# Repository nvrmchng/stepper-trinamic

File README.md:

# stepper-trinamic
Driving stepper motor with TMC2130 IC from TRINAMIC Motion.

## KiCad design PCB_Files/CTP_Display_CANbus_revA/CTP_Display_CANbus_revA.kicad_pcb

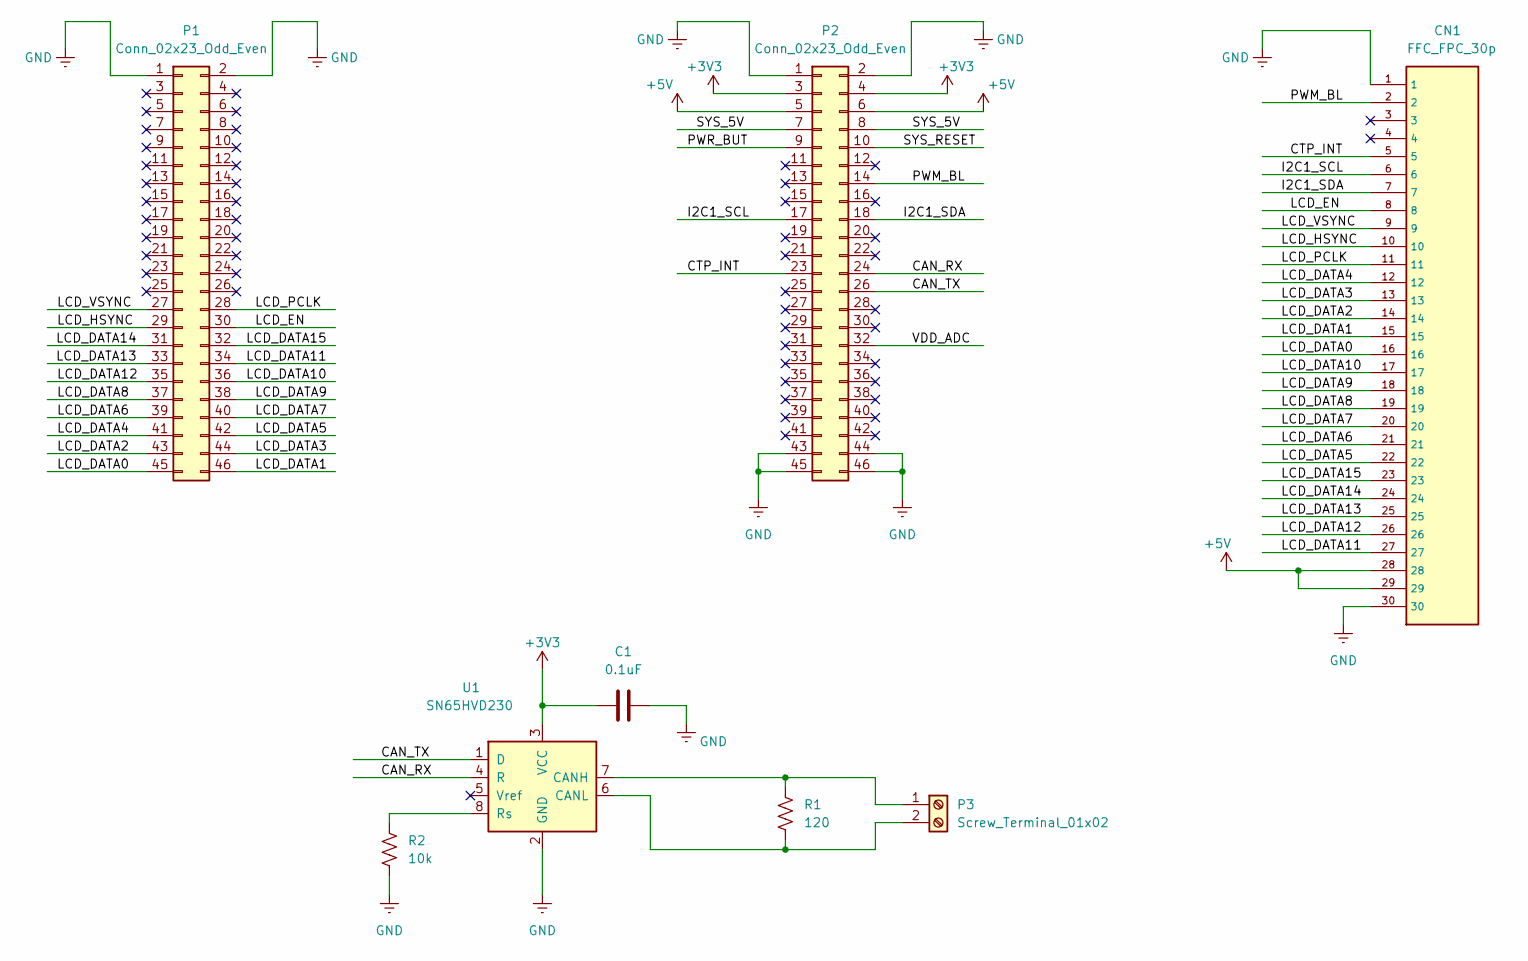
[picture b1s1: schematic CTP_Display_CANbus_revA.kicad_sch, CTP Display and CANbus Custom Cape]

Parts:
C1: 0.1uF; C_0603_1608Metric
CN1: FFC_FPC_30p; AMPHENOL_F32Q-1A7H1-11030
P1, P2: Conn_02x23_Odd_Even; HEADER_2X23_P2.54MM
P3: Screw_Terminal_01x02; TERM_BLK_2P_5MM_HORIZONTAL
R1: 120; R_0603_1608Metric_Pad0.98x0.95mm_HandSolder
R2: 10k; R_0603_1608Metric_Pad0.98x0.95mm_HandSolder
U1: SN65HVD230; SOIC-8_3.9x4.9mm_P1.27mm

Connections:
+3V3: C1.1, P2.3, P2.4, U1.3 (VCC)
+5V: CN1.28, CN1.29, P2.5, P2.6
/CAN_RX: P2.24, U1.4 (R)
/CAN_TX: P2.26, U1.1 (D)
/CTP_INT: CN1.5, P2.23
/I2C1_SCL: CN1.6, P2.17
/I2C1_SDA: CN1.7, P2.18
/LCD_DATA0: CN1.16, P1.45
/LCD_DATA1: CN1.15, P1.46
/LCD_DATA2: CN1.14, P1.43
/LCD_DATA3: CN1.13, P1.44
/LCD_DATA4: CN1.12, P1.41
/LCD_DATA5: CN1.22, P1.42
/LCD_DATA6: CN1.21, P1.39
/LCD_DATA7: CN1.20, P1.40
/LCD_DATA8: CN1.19, P1.37
/LCD_DATA9: CN1.18, P1.38
/LCD_DATA10: CN1.17, P1.36
/LCD_DATA11: CN1.27, P1.34
/LCD_DATA12: CN1.26, P1.35
/LCD_DATA13: CN1.25, P1.33
/LCD_DATA14: CN1.24, P1.31
/LCD_DATA15: CN1.23, P1.32
/LCD_EN: CN1.8, P1.30
/LCD_HSYNC: CN1.10, P1.29
/LCD_PCLK: CN1.11, P1.28
/LCD_VSYNC: CN1.9, P1.27
/PWM_BL: CN1.2, P2.14
/PWR_BUT: P2.9
/SYS_5V: P2.7, P2.8
/SYS_RESET: P2.10
/VDD_ADC: P2.32
GNDREF: C1.2, CN1.1, CN1.30, CN1.S1, CN1.S2, P1.1, P1.2, P2.1, P2.2, P2.43, P2.44, P2.45, P2.46, R2.2, U1.2 (GND)
unnamed: P3.1, R1.1, U1.7 (CANH)
unnamed: P3.2, R1.2, U1.6 (CANL)
unnamed: R2.1, U1.8 (Rs)

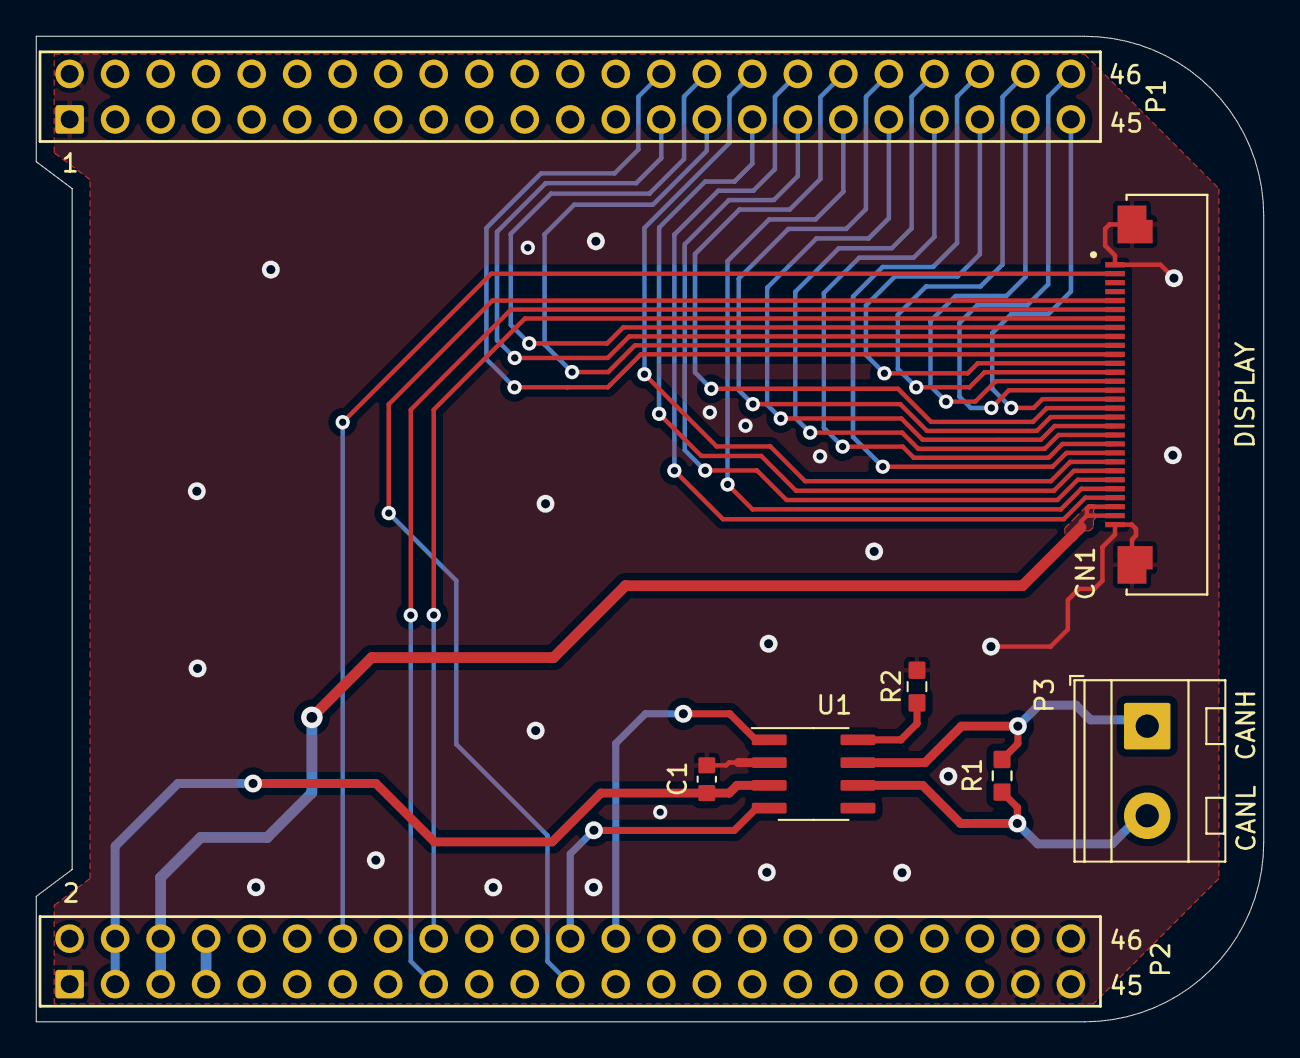
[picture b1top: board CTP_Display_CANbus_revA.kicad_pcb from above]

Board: 2 copper layers, 68.5 x 55.0 mm, 8 parts (0 on the bottom side), 33 nets.

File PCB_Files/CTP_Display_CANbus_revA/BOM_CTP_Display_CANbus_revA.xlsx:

| xxxx xxxx xxxxx xxPCS BOM (Sample Bill of Materials)
Quantity | Designator | Description | Footprint | Manufacturer | Part Number (Manufacturer) | Supplier | Buying Link as reference
1 | C1 | Capacitor Ceramic 0.1uF 50V X7R AEC-Q200 (Automotive) | 0603 (1608 Metric) | TDK Corporation | CGA3E2X7R1H104K080AA | Digikey
1 | CN1 | Conn FFC FPC 30Pos Slide Lock 0.5mm Pitch Top Contact | Surface Mount, Right Angle | Amphenol ICC (FCI) | F32Q-1A7H1-11030 | Digikey
2 | P1, P2 | Female Header Black 46Pos (2x23) 2.54mm Pitch Tin Contact | Through Hole | Samtec Inc. | SSQ-123-03-T-D | Digikey
1 | P3 | Screw Terminal Block Green 2Pos 5mm Pitch Horizontal | Through Hole | Wurth Elektronik | 691137710002 | Digikey
1 | R1 | Res 120 Ohm 1% +-100ppm 0.25W AEC-Q200 (Automotive) | 0603 (1608 Metric) | Vishay Dale | RCS0603120RFKEA | Digikey
1 | R2 | Res 10kOhm 5% +-100ppm 0.1W AEC-Q200 (Automotive) | 0603 (1608 Metric) | YAGEO | AC0603JR-0710KL | Digikey
1 | U1 | IC Transceiver CANbus 1 Mbps Half Duplex 3-3.6V Supply | SOIC-8 (3.9x4.9mm) | Texas Instruments | SN65HVD230DR | Digikey

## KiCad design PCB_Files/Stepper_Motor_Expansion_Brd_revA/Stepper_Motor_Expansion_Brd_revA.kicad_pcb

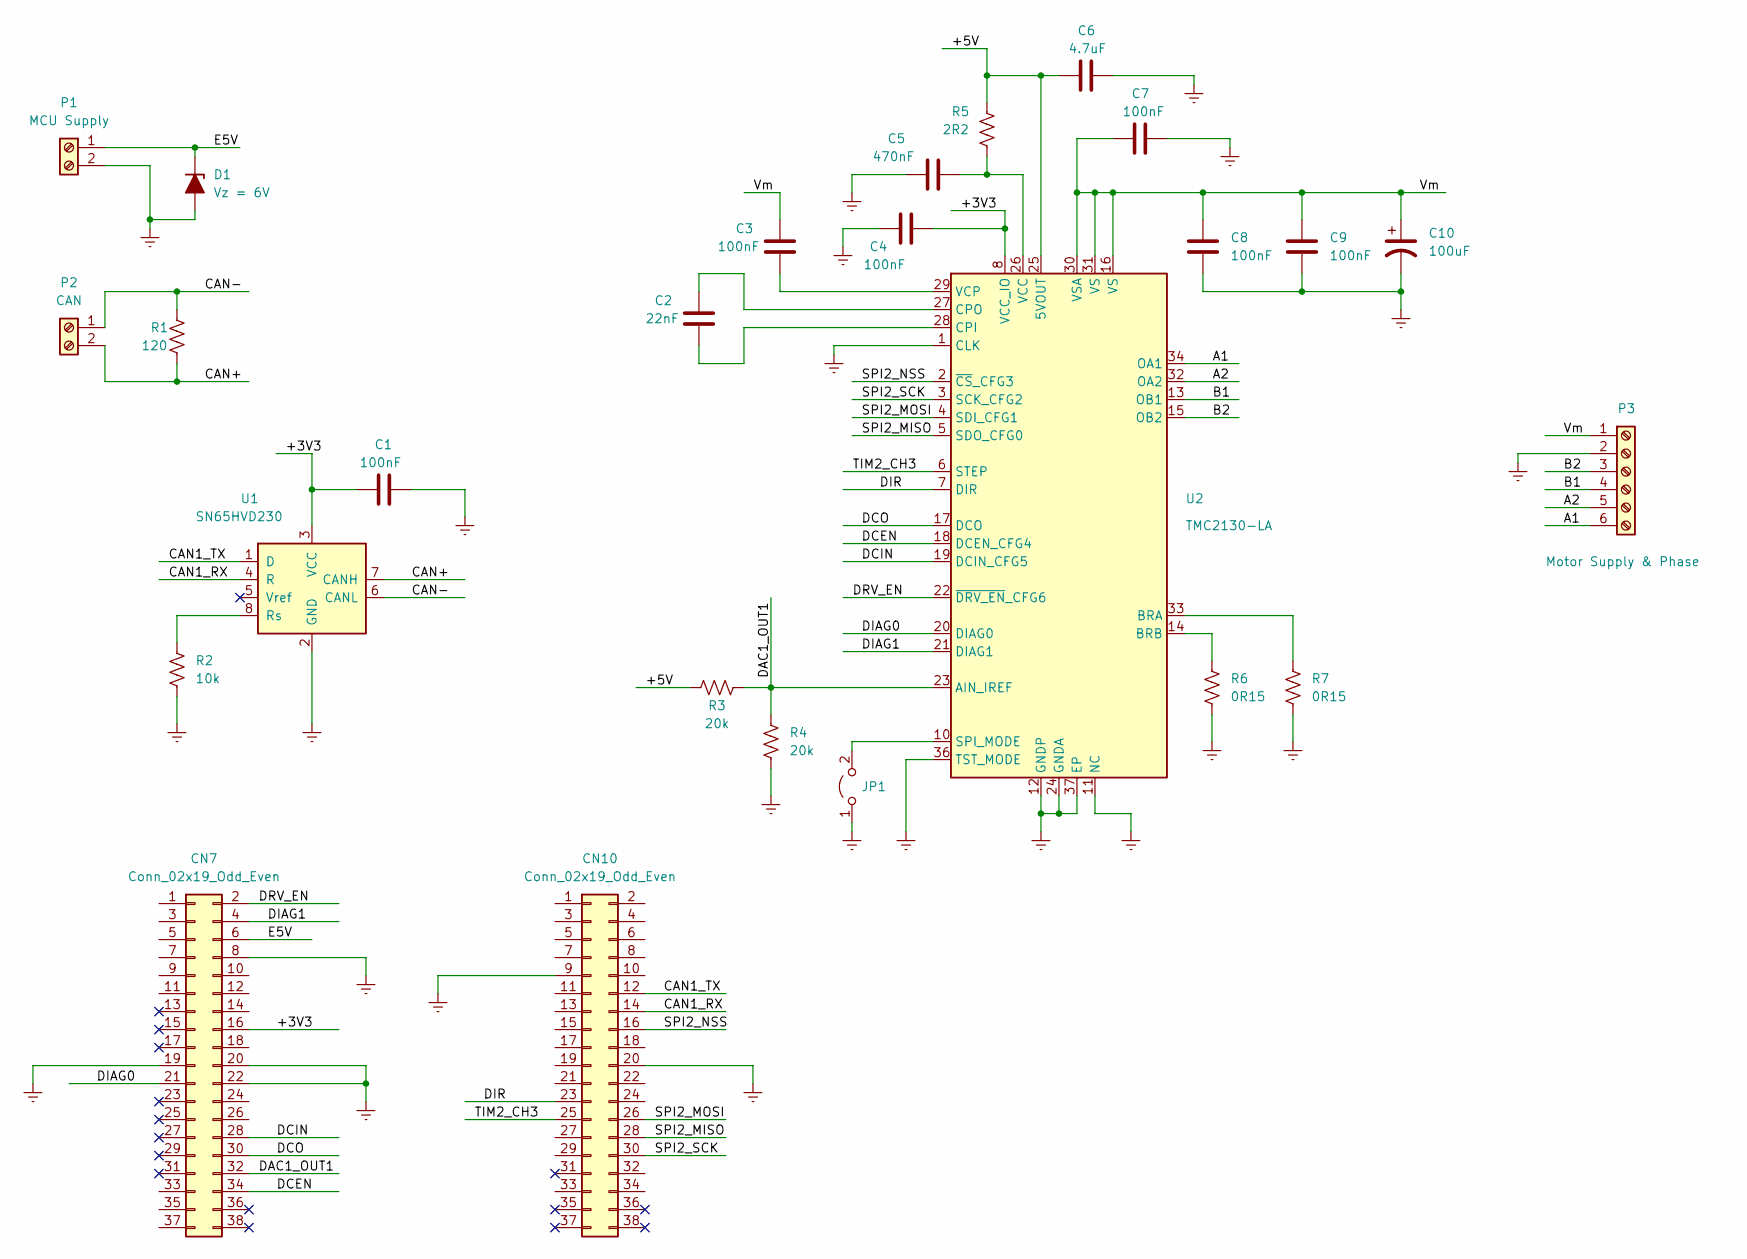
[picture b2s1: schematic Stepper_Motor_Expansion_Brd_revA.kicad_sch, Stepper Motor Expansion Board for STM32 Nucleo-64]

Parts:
C1, C3, C4, C7, C8, C9: 100nF; C_0402_1005Metric
C2: 22nF; C_0402_1005Metric
C5: 470nF; C_0603_1608Metric
C6: 4.7uF; C_0805_2012Metric
C10: 100uF; CP_Elec_6.3x7.7(EMZR500ARA101MF80G)
CN7, CN10: Conn_02x19_Odd_Even; Header_2x19_P2.54mm_Vertical(SAMTEC_SSW-119-01-F-D)
D1: Vz = 6V; D_SMB(DO-214AA)
JP1: Jumper_2_Open; PinHeader_1x02_P2.54mm_Vertical
P1: MCU Supply; TerminalBlock-2_P5.00mm(TB002-500-02BE)
P2: CAN; TerminalBlock-2_P3.50mm(OSTTE020104)
P3: Motor Supply & Phase; TerminalBlock_Wuerth-6_P5.00mm(1137710006)
R1: 120; R_0603_1608Metric_Pad0.98x0.95mm_HandSolder
R2: 10k; R_0603_1608Metric_Pad0.98x0.95mm_HandSolder
R3, R4: 20k; R_0603_1608Metric_Pad0.98x0.95mm_HandSolder
R5: 2R2; R_0603_1608Metric_Pad0.98x0.95mm_HandSolder
R6, R7: 0R15; R_0805_2012Metric_Pad1.20x1.40mm_HandSolder
U1: SN65HVD230; SOIC-8_3.9x4.9mm_P1.27mm
U2: TMC2130-LA; QFN-36-1EP_5x6mm_P0.5mm_EP3.6x4.1mm

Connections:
/+3V3: C1.2, C4.1, CN7.16, U1.3 (VCC), U2.8 (VCC_IO)
/+5V: C6.1, R3.1, R5.1, U2.25 (5VOUT)
/A1: P3.6, U2.34 (OA1)
/A2: P3.5, U2.32 (OA2)
/B1: P3.4, U2.13 (OB1)
/B2: P3.3, U2.15 (OB2)
/CAN1_RX: CN10.14, U1.4 (R)
/CAN1_TX: CN10.12, U1.1 (D)
/CAN+: P2.2, R1.2, U1.7 (CANH)
/CAN-: P2.1, R1.1, U1.6 (CANL)
/DAC1_OUT1: CN7.32, R3.2, R4.1, U2.23 (AIN_IREF)
/DCEN: CN7.34, U2.18 (DCEN_CFG4)
/DCIN: CN7.28, U2.19 (DCIN_CFG5)
/DCO: CN7.30, U2.17 (DCO)
/DIAG0: CN7.21, U2.20 (DIAG0)
/DIAG1: CN7.4, U2.21 (DIAG1)
/DIR: CN10.23, U2.7 (DIR)
/DRV_EN: CN7.2, U2.22 (~DRV_EN_CFG6)
/E5V: CN7.6, D1.1 (K), P1.1
/SPI2_MISO: CN10.28, U2.5 (SDO_CFG0)
/SPI2_MOSI: CN10.26, U2.4 (SDI_CFG1)
/SPI2_NSS: CN10.16, U2.2 (~CS_CFG3)
/SPI2_SCK: CN10.30, U2.3 (SCK_CFG2)
/TIM2_CH3: CN10.25, U2.6 (STEP)
/Vm: C3.2, C7.1, C8.1, C9.1, C10.1, P3.1, U2.16 (VS), U2.30 (VSA), U2.31 (VS)
GND: C1.1, C4.2, C5.2, C6.2, C7.2, C8.2, C9.2, C10.2, CN7.8, CN7.19, CN7.20, CN7.22, CN10.9, CN10.20, D1.2 (A), JP1.1 (A), P1.2, P3.2, R2.2, R4.2, R6.2, R7.2, U1.2 (GND), U2.1 (CLK), U2.11 (NC), U2.12 (GNDP), U2.24 (GNDA), U2.35 (GNDP), U2.36 (TST_MODE), U2.37 (EP)
unnamed: C2.1, U2.28 (CPI)
unnamed: C2.2, U2.27 (CPO)
unnamed: C3.1, U2.29 (VCP)
unnamed: C5.1, R5.2, U2.26 (VCC)
unnamed: JP1.2 (B), U2.10 (SPI_MODE)
unnamed: R2.1, U1.8 (Rs)
unnamed: R6.1, U2.14 (BRB)
unnamed: R7.1, U2.33 (BRA)

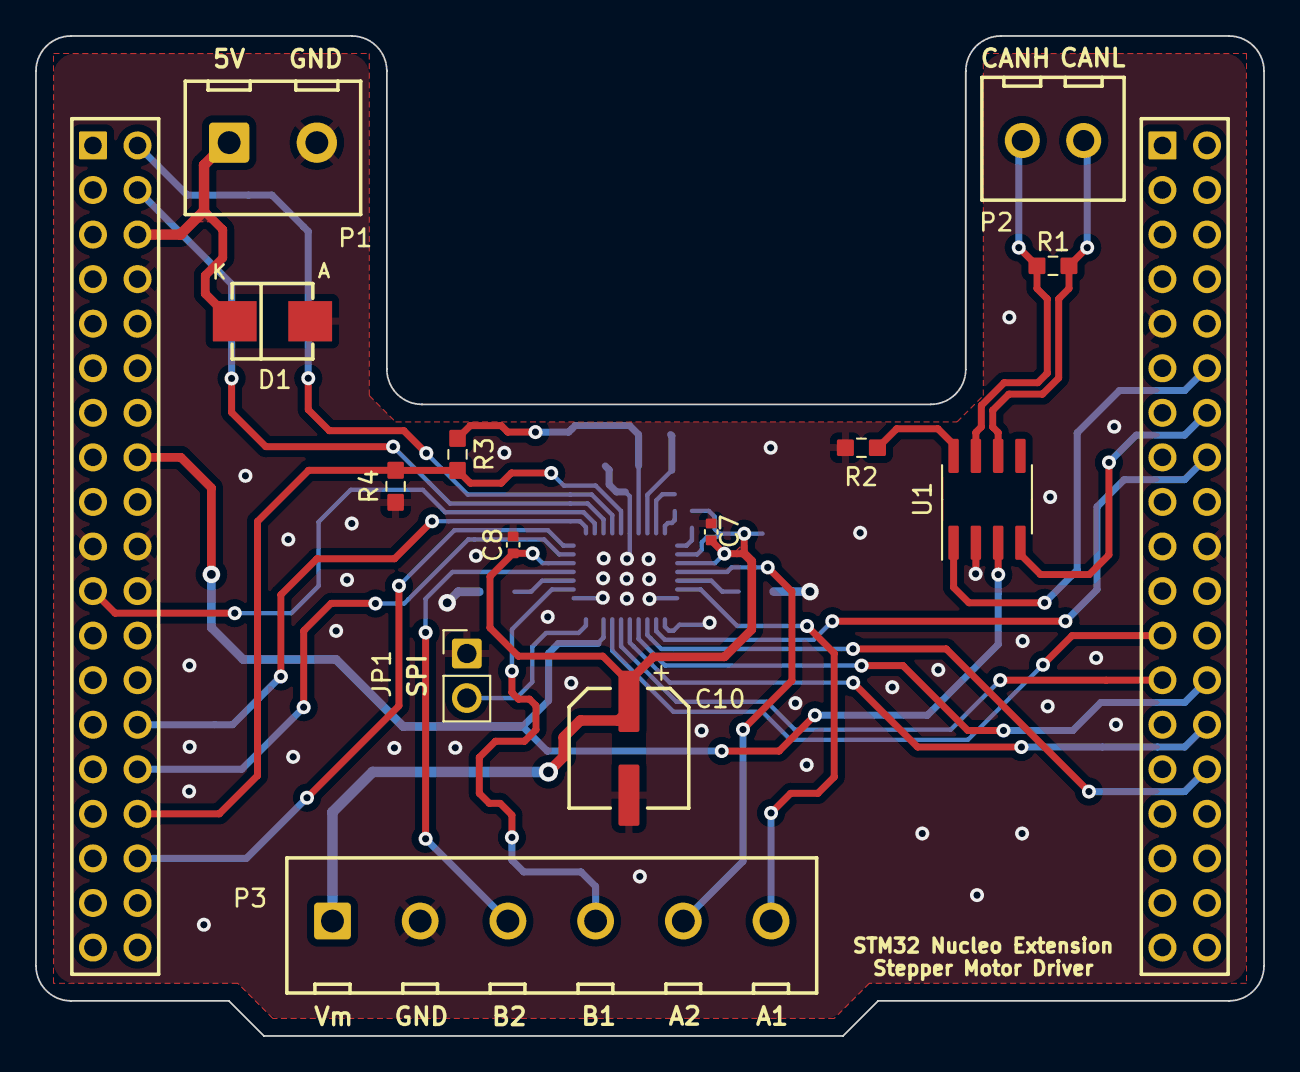
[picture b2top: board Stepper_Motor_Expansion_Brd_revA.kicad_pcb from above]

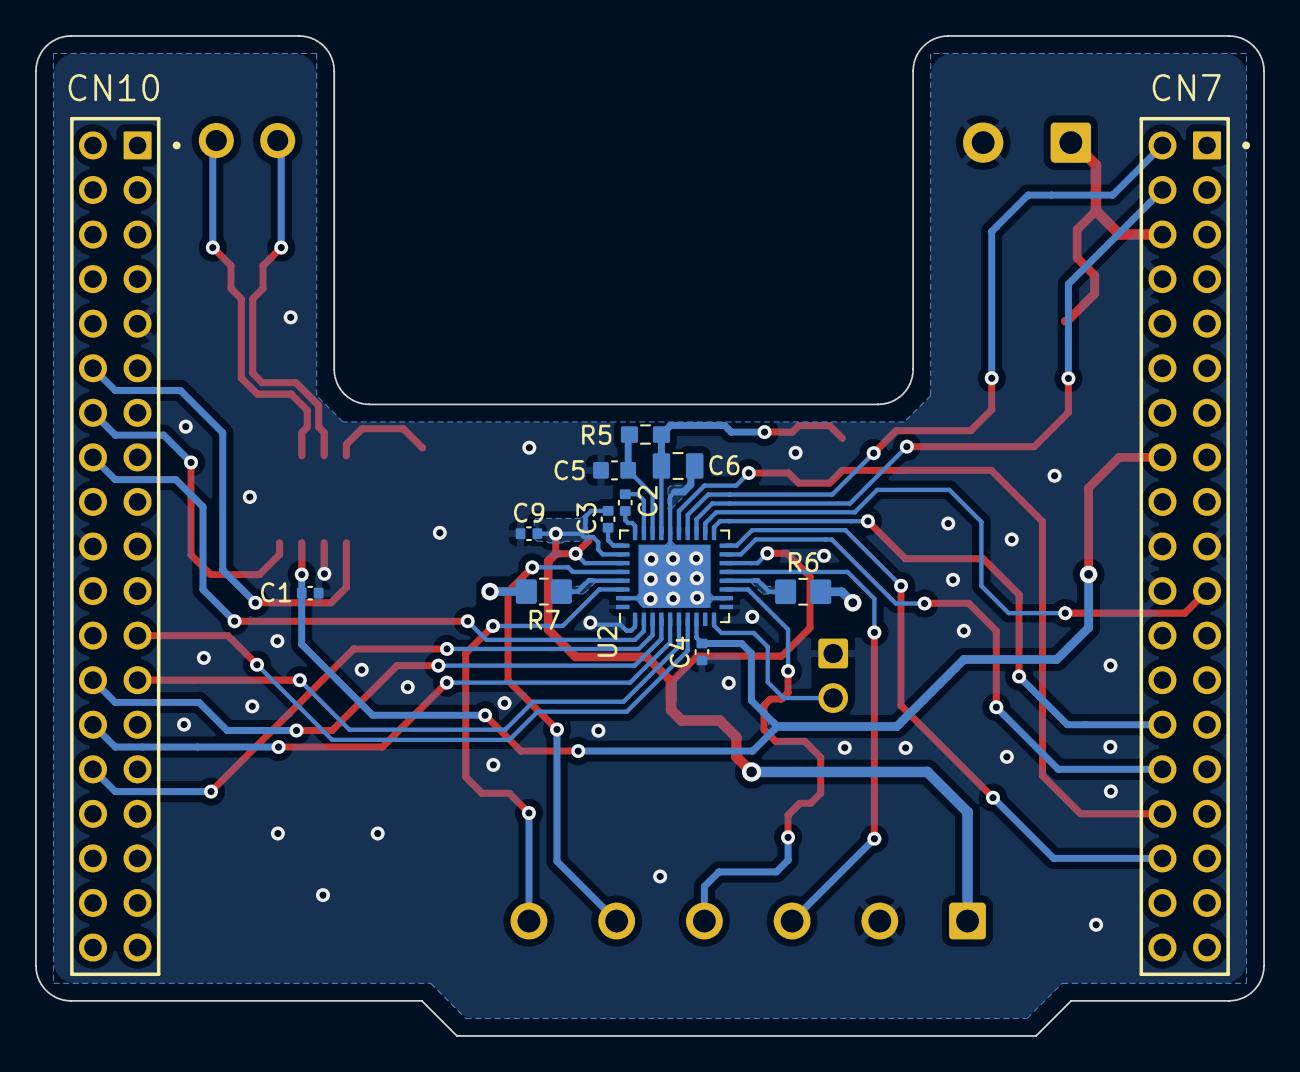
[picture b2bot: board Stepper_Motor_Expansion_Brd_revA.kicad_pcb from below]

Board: 2 copper layers, 70.0 x 57.0 mm, 26 parts (13 on the bottom side), 34 nets.

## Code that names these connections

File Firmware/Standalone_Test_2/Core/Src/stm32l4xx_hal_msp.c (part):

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
    __HAL_RCC_GPIOA_CLK_ENABLE();
    /**CAN1 GPIO Configuration
    PA11     ------> CAN1_RX
    PA12     ------> CAN1_TX
    */
    GPIO_InitStruct.Pin = GPIO_PIN_11|GPIO_PIN_12;
    GPIO_InitStruct.Mode = GPIO_MODE_AF_PP;
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    __HAL_RCC_CAN1_CLK_DISABLE();

    /**CAN1 GPIO Configuration
    PA11     ------> CAN1_RX
    PA12     ------> CAN1_TX
    */
    HAL_GPIO_DeInit(GPIOA, GPIO_PIN_11|GPIO_PIN_12);

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
    __HAL_RCC_GPIOA_CLK_ENABLE();
    /**DAC1 GPIO Configuration
    PA4     ------> DAC1_OUT1
    */
    GPIO_InitStruct.Pin = GPIO_PIN_4;
    GPIO_InitStruct.Mode = GPIO_MODE_ANALOG;
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    __HAL_RCC_DAC1_CLK_DISABLE();

    /**DAC1 GPIO Configuration
    PA4     ------> DAC1_OUT1
    */
    HAL_GPIO_DeInit(GPIOA, GPIO_PIN_4);

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
    __HAL_RCC_GPIOB_CLK_ENABLE();
    /**TIM2 GPIO Configuration
    PB10     ------> TIM2_CH3
    */
    GPIO_InitStruct.Pin = GPIO_PIN_10;
    GPIO_InitStruct.Mode = GPIO_MODE_AF_PP;
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
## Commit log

2024-09-15 Create Stepper_Motor_Expansion_Brd_revA-top-pos
2024-09-15 Update Stepper_Motor_Expansion_Brd_revA-top-pos
2024-09-15 Create fp-info-cache
2024-09-15 add CTP_Display_CANbus_revA to PCB_Files
2024-09-15 Add Firmware folder
2024-09-15 Push Software ui sources
    Qt on Windows & BBB Linux
2024-09-15 add some pictures of board
2024-09-15 Create top side
2024-09-15 add some screenshots
2024-09-16 add test setup

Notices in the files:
Firmware/Standalone_Test_2/Core/Src/stm32l4xx_hal_msp.c:
Copyright (c) 2024 STMicroelectronics.
All rights reserved.
This software is licensed under terms that can be found in the LICENSE file
